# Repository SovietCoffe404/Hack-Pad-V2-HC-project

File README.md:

# HACK-PAD V2

Hiii, well this is my second version of the Hack Pad since the other one was kinda lame though, so I added new functions to it so it's more fun and useful. You can check out the functions down here :D

# Based on:
**https://hackpad.hackclub.com**

## What it does

- 🖥️ **Custom screen** — Showing anything u want, text or image. Upload it by the PC app!
- ⌨️ **4 keys with editable macros** — U can change what every key does, like copy, paste, undo, etc.
- 🌈 **RGB LEDs with configurable color** — Also custom! choose the color u want in the app.
- 🎮 **Secret minigame** — Snake hidden inside the pad itself, with the option to add more games if wanted ˙𐃷˙ 

  `Hint`: Press all keys down at the same time

- 🕹️ **Extra minigames on the PC** — U can add more minigames!
- 🔌 **USB cable** — Only used to configure the pad from the PC app.
- 🔋 **Battery** (14500 Li-ion + TP4056 charging) — u can replace it whenever it's needed.

## Repo structure

```
HACK-PAD/
├── firmware/     C++ firmware (PlatformIO) flashed onto the XIAO
├── pc_app/       Desktop app in Python to configure the pad
├── hardware/     KiCAD and Fusion project (schematic, PCB, 3D models)
| ├── PCB/        KiCAD project
| └── CAD/        3D models
└── production/   Files for manufacturing (Gerber and .STEP files)
```

Each folder has its own README with the details, such like the PINOUT and clarifications about some things you may have doubts on :) 

## Pinout (Seeed XIAO ESP32-C3)

| XIAO pin | Connected to |
|---|---|
| D0–D3 | Buttons SW1–SW4 |
| D4 (SDA) | Data line for the 6 SK6812 LEDs (in parallel, all the same color) |
| D5 (SCL) | OLED RST |
| D6 (TX) | OLED DC |
| D8 (SCK) | OLED SCK |
| D9 (MISO) | OLED CS |
| D10 (MOSI) | OLED MOSI/DIN |

## Communication protocol

The PC app talks to the pad using plain text over USB. The full commands are in the firmware's README, but right here's a quick summary:

```
PING · SET_TEXT · SET_MACRO · SET_COLOR · SET_BRIGHTNESS · SAVE · GET_CONFIG · IMG_START
```
# BOM — HACK-PAD V2

## On-board (populated on the HACK-PAD PCB)

| RefDes | Description | Manufacturer / Part | Qty | Unit Price | Line Total | Supplier |
|---|---|---|---|---|---|---|
| U1 | XIAO ESP32-C3 module (RISC-V, WiFi+BLE) | [Seeed Studio XIAO ESP32C3](https://www.seeedstudio.com/Seeed-XIAO-ESP32C3-p-5431.html) | 1 | $4.99 | $4.99 | Seeed Studio |
| U2 (SCREEN) | 1.5" 128x128 RGB OLED, SPI (SSD1351) | [Waveshare 1.5inch RGB OLED Module](https://www.waveshare.com/1.5inch-rgb-oled-module.htm) | 1 | $20.99 | $20.99 | Waveshare |
| SW1–SW4 | Cherry MX mechanical switch, PCB mount | Cherry MX (any linear/tactile variant) | 4 | $0.35 | $1.40 | [MechanicalKeyboards.co](https://mechanicalkeyboards.com/collections/cherry-switches) |
| D1–D6 | RGB LED, PLCC4 5x5mm | [OPSCO SK6812](https://www.lcsc.com/product-detail/RGB-LEDs-Built-in-IC_OPSCO-Optoelectronics-SK6812_C5378720.html) | 6 | $0.07 | $0.42 | LCSC |
| R1 | Resistor, 330Ω, 1206 SMD | Generic 1206 | 1 | $0.02 | $0.02 | LCSC |
| C1 | Capacitor, 1206 SMD (schematic value: 100nF) | Generic 1206 | 1 | $0.10 | $0.10 | LCSC |
| — | Custom 2-layer PCB | Fabricated from `hardware/*.kicad_pcb` | 1 | $5.00 | $5.00 | [JLCPCB](https://jlcpcb.com/) |

## Off-board (wired in via the VIN header, not on the PCB)

| Description | Manufacturer / Part | Qty | Unit Price | Line Total | Supplier |
|---|---|---|---|---|---|
| TP4056 protected Li-ion charging module (USB-C) | Generic, with protection | 1 | $1.99 | $1.99 | [AliExpress](https://es.aliexpress.com/item/1005008927476478.html?spm=a2g0o.productlist.main.11.54d658c9kT2wZy&algo_pvid=a029871f-9f27-47d8-8982-c2caec298b3c&algo_exp_id=a029871f-9f27-47d8-8982-c2caec298b3c-10&pdp_ext_f=%7B"order"%3A"-1"%2C"spu_best_type"%3A"price"%2C"eval"%3A"1"%2C"fromPage"%3A"search"%7D&pdp_npi=6%40dis%21USD%211.74%211.74%21%21%2111.65%2111.65%21%402103081117886428617766381e0fd2%2112000047233885048%21sea%21MX%217457249807%21X%211%210%21n_tag%3A-29919%3Bd%3Aa5ac4bc3%3Bm03_new_user%3A-29895&curPageLogUid=Qe5zJJ3YYP9L&utparam-url=scene%3Asearch%7Cquery_from%3A%7Cx_object_id%3A1005008927476478%7C_p_origin_prod%3A) |
| 14500 Li-ion rechargeable cell, 3.7V | Generic protected cell | 1 | $6.99 | $6.99 | [Mercado Libre](https://www.mercadolibre.com.mx/bateria-recargable-14500-37v-aa-pilas-paquete-de-5pz/up/MLMU444769361#polycard_client=search-desktop&float_highlight=price_dropped&be_origin=backend&overlay_label=not_apply&search_layout=grid&position=41&type=product&tracking_id=673afcfe-ed87-421f-a0eb-6174e7703da4&wid=MLM1369192975&sid=search) |
| Jumper wires | Generic | 1 | $4.99 | $4.99 | [Amazon](https://www.amazon.com.mx/Pruebas-Opcionales-Surtido-Multicolo-Macho-Macho/dp/B0F8K2V18S/ref=sr_1_12?__mk_es_MX=ÅMÅŽÕÑ&crid=2FS9WYDOSLELE&dib=eyJ2IjoiMSJ9.crRcIveGq5Dw6rDP8TsgO1dETPBiBBGED-DrAo09-GRAilTQacxppwqxDViYUAY-jR3B_KcH6lcgj1K-tfIU84nO_ciKgtcC6ZQgJShRqth2BKZDS8j-fq_M_uzVEkaHaFCv_eAJsr9aoTBhb2Q0aKqUz7Y5OnCptMHbCzkuZ_h_VzxIN1AAuZdxH5VF6VKSBQSK2pvNOzy734qRTMIaI2mt8i6tOXdPIBouzRZpiuLq350KXtcUkKXS91tydHXCoizO2jGQa5hunUlGqmn3LnBxT9KSzTnNlR9Szy-x-m0.PVsSNEvhWFqVmlIMK_lOHYp4xiS0gu-wmmEk9sWaAvc&dib_tag=se&keywords=cable%2Bdupont&qid=1788641719&sprefix=cables%2Bdupont%2Caps%2C160&sr=8-12&th=1) |

## Enclosure (not included in the subtotal)

| Description | Source | Cost |
|---|---|---|
| 3D-printed case (`hardware/3D_HACK-PAD_Printing.step`) | Print it by yourself, or a service like JLC3DP |

## Subtotal

**On-board + off-board parts: ≈ $47.55** (excludes shipping, taxes, and the case)

## Screen Shots!

## License

MIT — see [`LICENSE`](LICENSE). Use, modify, and share the project
freely, with or without credit.

## ★ Special thanks to:
`https://www.printables.com/@wireva` for the keycaps 3d model! :D

`hackclub.com` for the DIY guide and funding! <3

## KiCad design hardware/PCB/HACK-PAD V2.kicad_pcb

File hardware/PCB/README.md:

# hardware/

KiCad 8 project for the HACK-PAD V2 (4-key macropad with color OLED screen
and RGB LEDs).

| File | What it is |
|---|---|
| `HACK-PAD_V2.kicad_pro` | Project — open this one from KiCad |
| `HACK-PAD_V2.kicad_sch` | Schematic |
| `HACK-PAD_V2.kicad_pcb` | Board layout |
| `HACK-PAD_V2.kicad_prl` | Local project preferences (not critical) |
| `fp-lib-table` | Footprint library table used by the project |
| `3D_HACK-PAD_Assembled.step` | 3D model with all components mounted — for visualizing/rendering the full pad |
| `3D_HACK-PAD_Printing.step` | Simplified 3D model (no electronics) — for 3D-printing the case/enclosure |

## XIAO module: SAMD21 (board) → ESP32-C3 (current firmware)

The schematic/PCB were originally designed around the **Seeed XIAO
SAMD21** footprint. The current firmware (`firmware/`) targets the
**Seeed XIAO ESP32-C3** for Bluetooth.

**No board redesign needed**: the whole XIAO family (SAMD21, ESP32-C3,
ESP32-S3, nRF52840, RP2040...) shares the same 14-pad castellated
footprint (21×17.5mm), and it's confirmed that the hardware SPI pins land
in the same spots (D8=SCK, D9=MISO, D10=MOSI) on both the SAMD21 and the
ESP32-C3 — the module can be swapped on the physical board without
touching the wiring.

The only thing left "untidy" is cosmetic: the schematic symbol still says
`MOUDLE-SEEEDUINO-XIAO` (its original value). If you want the BOM/schematic
to reflect the real chip, in KiCad: `Edit > Change Symbols...` and update
the `Value` to something like `XIAO-ESP32C3`. Not required for the board
to work, just project tidiness.

## Pinout (applies to any XIAO module you use)

| XIAO pin | Connected to |
|---|---|
| D0–D3 | Buttons SW1–SW4 (to GND, with internal pull-up) |
| D4 (SDA) | Data line for the 6 SK6812 LEDs — **all 6 share the same DIN in parallel on purpose**, which is why they always show the same color |
| D5 (SCL) | OLED RST |
| D6 (TX) | OLED DC |
| D8 (SCK) | OLED SCK (hardware SPI) |
| D9 (MISO) | OLED CS |
| D10 (MOSI) | OLED MOSI/DIN (hardware SPI) |

## Notes

- The screen is a Waveshare 1.5" 128x128 RGB OLED (SSD1351 driver).
- Power: 14500 Li-ion battery + TP4056 charge/protection module.
- The `*-backups/` folder KiCad automatically generates on save is
  excluded from the repo (see the root `.gitignore`) — no need to version it.

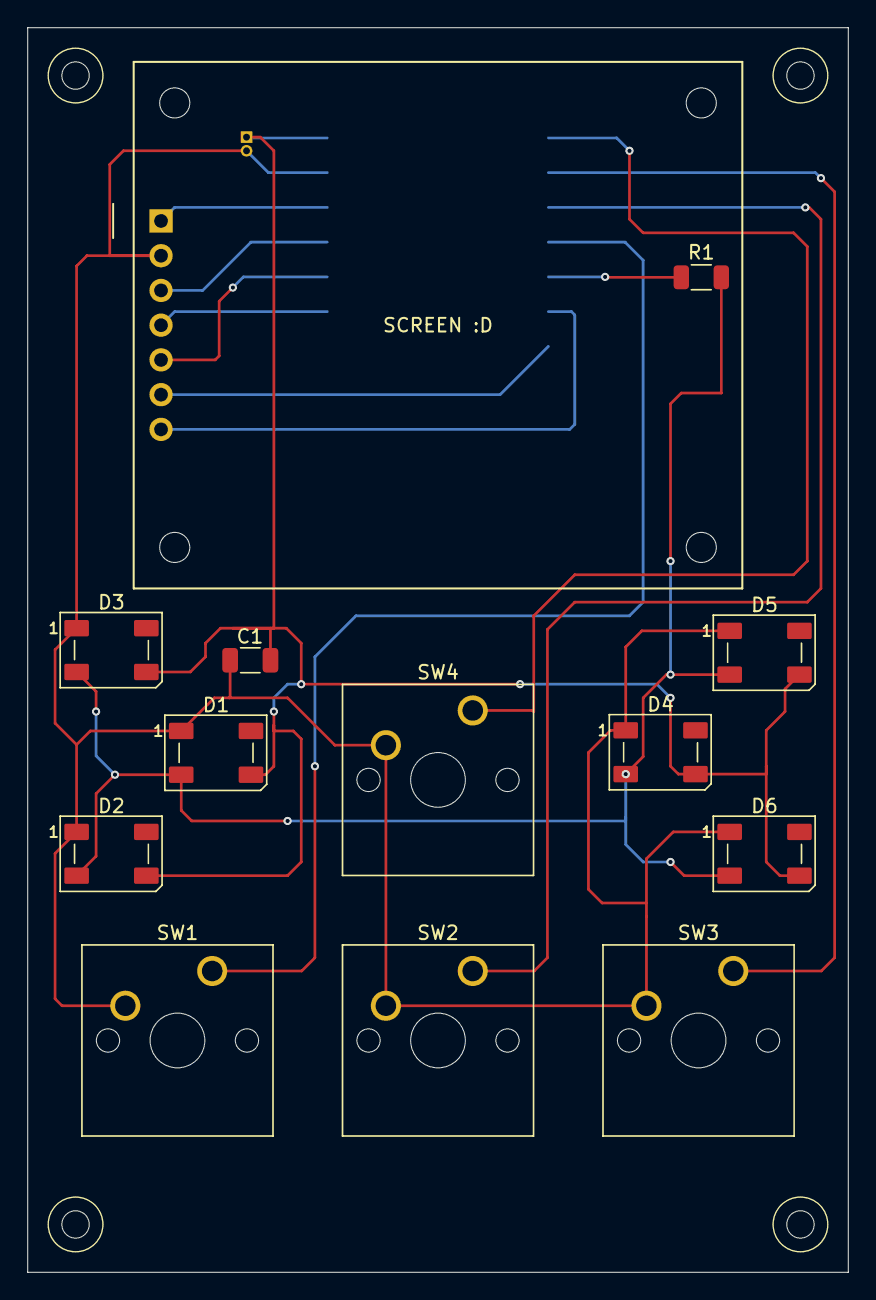
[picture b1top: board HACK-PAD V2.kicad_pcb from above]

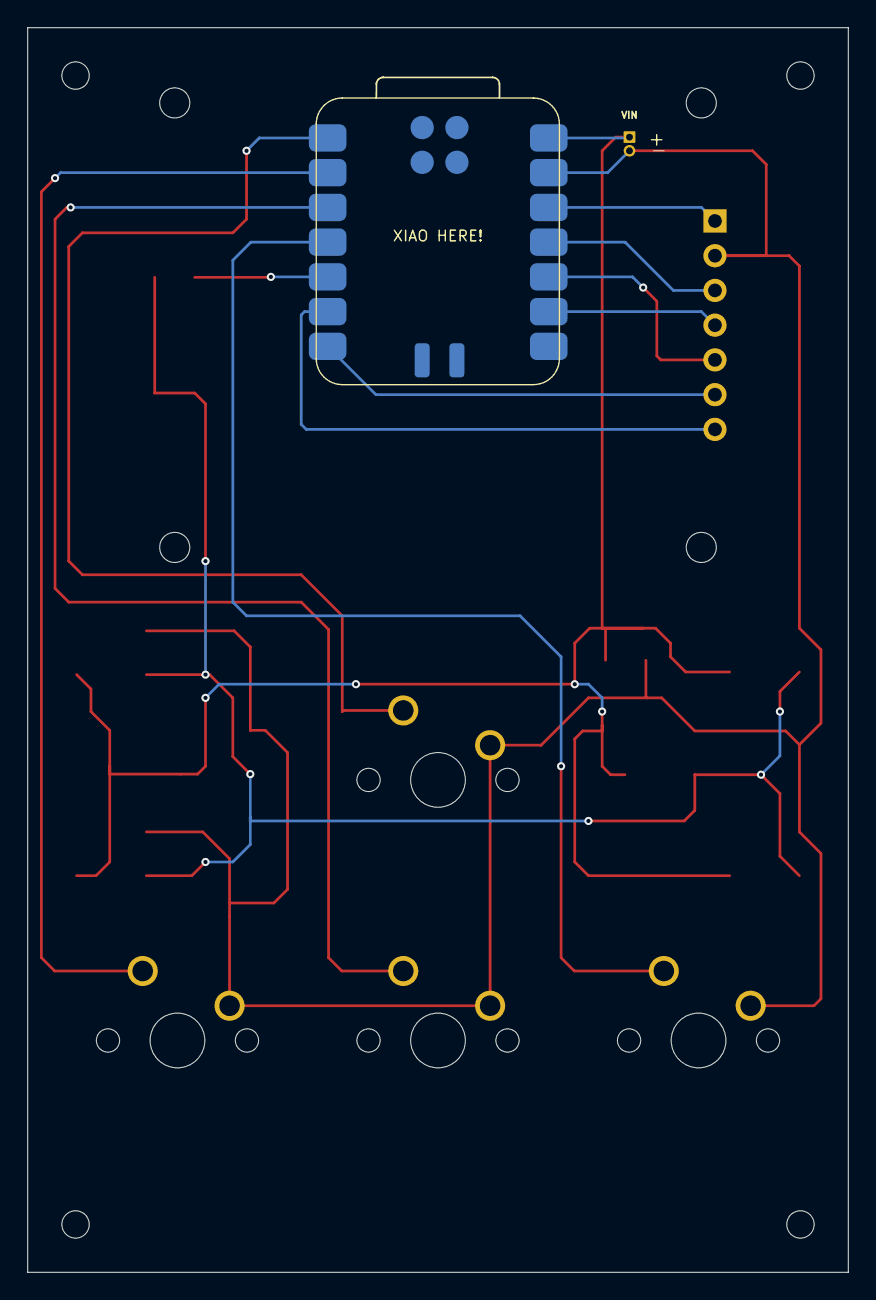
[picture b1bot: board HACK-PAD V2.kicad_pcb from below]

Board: 2 copper layers, 60.0 x 91.0 mm, 15 parts (2 on the bottom side), 13 nets.

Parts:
C1: 100 nF; C_1206_3216Metric
D1, D2, D3, D4, D5, D6: LED; LED_OPSCO_SK6812_PLCC4_5.0x5.0mm_P3.1mm
R1: 330 ohms; R_1206_3216Metric
SCREEN :D: OLED_1.5inch_RGB_SPI; Waveshare_OLED_1.5inch_ModuleB (5)
SW1, SW2, SW3, SW4: SW_Push; SW_Cherry_MX_1.00u_PCB
VIN: Screw_Terminal_01x02; PinHeader_1x02_P1.00mm_Vertical
XIAO HERE!: MOUDLE-SEEEDUINO-XIAO; XIAO-SAMD21-SMD

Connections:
+5V: C1.1, D1.3, D2.3, D3.3, D4.3, D5.3, D6.3, VIN.1
/CS: SCREEN :D.5 (CS), XIAO HERE!.10 (PA5_A9_D9_MISO)
GND: C1.2, D1.1 (K), D2.1 (K), D3.1 (K), D4.1 (K), D5.1 (K), D6.1 (K), SCREEN :D.2 (GND), SW1.2, SW2.2, SW3.2, SW4.2, VIN.2
unnamed: D1.2 (A), D2.2 (A), D3.2 (A), D4.2 (A), D5.2 (A), D6.2 (A), R1.2
unnamed: SW4.1, XIAO HERE!.1 (PA02_A0_D0)
unnamed: SW3.1, XIAO HERE!.2 (PA4_A1_D1)
unnamed: SCREEN :D.3 (DIN), XIAO HERE!.11 (PA6_A10_D10_MOSI)
unnamed: SCREEN :D.4 (CLK), XIAO HERE!.9 (PA7_A8_D8_SCK)
unnamed: R1.1, XIAO HERE!.5 (PA8_A4_D4_SDA)
unnamed: SCREEN :D.7 (RST), XIAO HERE!.6 (PA9_A5_D5_SCL)
unnamed: SW2.1, XIAO HERE!.3 (PA10_A2_D2)
unnamed: SW1.1, XIAO HERE!.4 (PA11_A3_D3)
unnamed: SCREEN :D.6 (DC), XIAO HERE!.7 (PB08_A6_D6_TX)
